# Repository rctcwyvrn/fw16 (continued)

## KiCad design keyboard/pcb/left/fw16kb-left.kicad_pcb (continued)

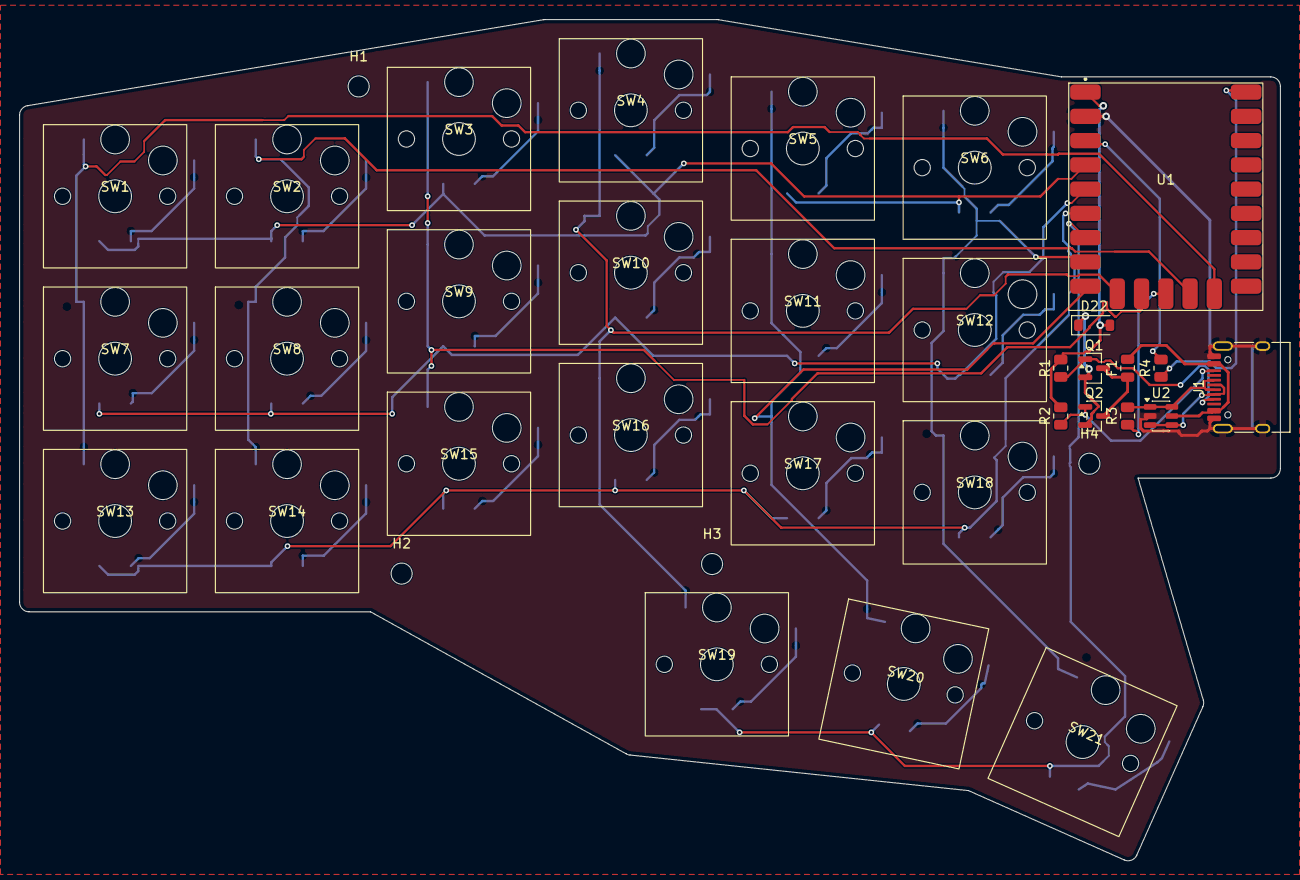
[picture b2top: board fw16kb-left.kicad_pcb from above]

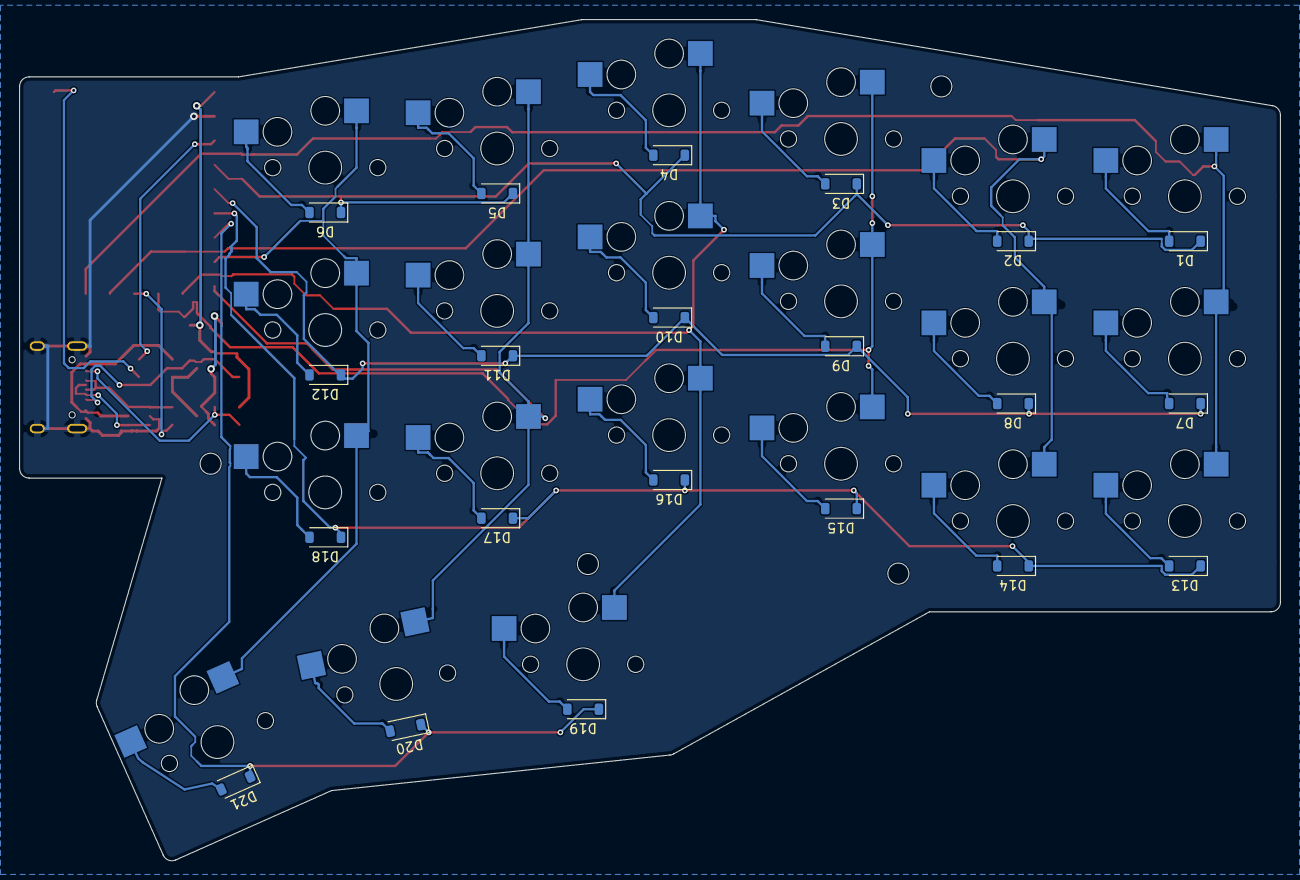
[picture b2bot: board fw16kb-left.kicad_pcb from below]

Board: 2 copper layers, 132.0 x 88.1 mm, 57 parts (21 on the bottom side), 43 nets.

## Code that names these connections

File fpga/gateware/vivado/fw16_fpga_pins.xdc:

# GENERATED by gateware/vivado/pins/pins_xdc.exe from bay/card/fpga/pinplan.csv — do not edit.
# Regenerate: dune build @runtest --auto-promote (from fpga/).
set_property PACKAGE_PIN P2 [get_ports {pci_exp_rxp[0]}]
# GT_RX0_N (P1): board only, no port
set_property PACKAGE_PIN T2 [get_ports {pci_exp_rxp[1]}]
# GT_RX1_N (T1): board only, no port
set_property PACKAGE_PIN V2 [get_ports {pci_exp_rxp[2]}]
# GT_RX2_N (V1): board only, no port
set_property PACKAGE_PIN Y2 [get_ports {pci_exp_rxp[3]}]
# GT_RX3_N (Y1): board only, no port
set_property PACKAGE_PIN R5 [get_ports {pci_exp_txp[0]}]
# GT_TX0_N (R4): board only, no port
set_property PACKAGE_PIN U5 [get_ports {pci_exp_txp[1]}]
# GT_TX1_N (U4): board only, no port
set_property PACKAGE_PIN W5 [get_ports {pci_exp_txp[2]}]
# GT_TX2_N (W4): board only, no port
set_property PACKAGE_PIN AA5 [get_ports {pci_exp_txp[3]}]
# GT_TX3_N (AA4): board only, no port
set_property PACKAGE_PIN V7 [get_ports {sys_clk_p}]
# GT_REFCLK0_N (V6): board only, no port
# GT_REFCLK1_P (T7): board only, no port
# GT_REFCLK1_N (T6): board only, no port
# MGT_RREF (AD9): board only, no port
# MGT_AVTTRCAL (AD8): board only, no port
set_property PACKAGE_PIN AC13 [get_ports {clk100m}]
set_property IOSTANDARD LVCMOS33 [get_ports {clk100m}]
set_property PACKAGE_PIN AF14 [get_ports {sys_rst_n}]
set_property IOSTANDARD LVCMOS33 [get_ports {sys_rst_n}]
set_property PACKAGE_PIN AF15 [get_ports {clkreq_n}]
set_property IOSTANDARD LVCMOS33 [get_ports {clkreq_n}]
set_property PACKAGE_PIN AE13 [get_ports {th_alert}]
set_property IOSTANDARD LVCMOS33 [get_ports {th_alert}]
set_property PACKAGE_PIN AF13 [get_ports {th_overt}]
set_property IOSTANDARD LVCMOS33 [get_ports {th_overt}]
set_property PACKAGE_PIN AD15 [get_ports {sense_scl}]
set_property IOSTANDARD LVCMOS33 [get_ports {sense_scl}]
set_property PACKAGE_PIN AE15 [get_ports {sense_sda}]
set_property IOSTANDARD LVCMOS33 [get_ports {sense_sda}]
set_property PACKAGE_PIN AD14 [get_ports {sense_alert_n}]
set_property IOSTANDARD LVCMOS33 [get_ports {sense_alert_n}]
set_property PACKAGE_PIN AB15 [get_ports {pps_in}]
set_property IOSTANDARD LVCMOS33 [get_ports {pps_in}]
set_property PACKAGE_PIN W12 [get_ports {led_hb}]
set_property IOSTANDARD LVCMOS33 [get_ports {led_hb}]
set_property PACKAGE_PIN W13 [get_ports {led_link}]
set_property IOSTANDARD LVCMOS33 [get_ports {led_link}]
